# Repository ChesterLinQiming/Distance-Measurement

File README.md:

# Distance-Measurement

This project use GP2Y0A02YK0F which is Distance Measuring Sensor to measure the distance.

The range of it is 20-150cm.

The Circuit was designed by Qiming Lin.

This project also use AD7705, which is a two channel sigma delta converter, to convert the voltage from sensor

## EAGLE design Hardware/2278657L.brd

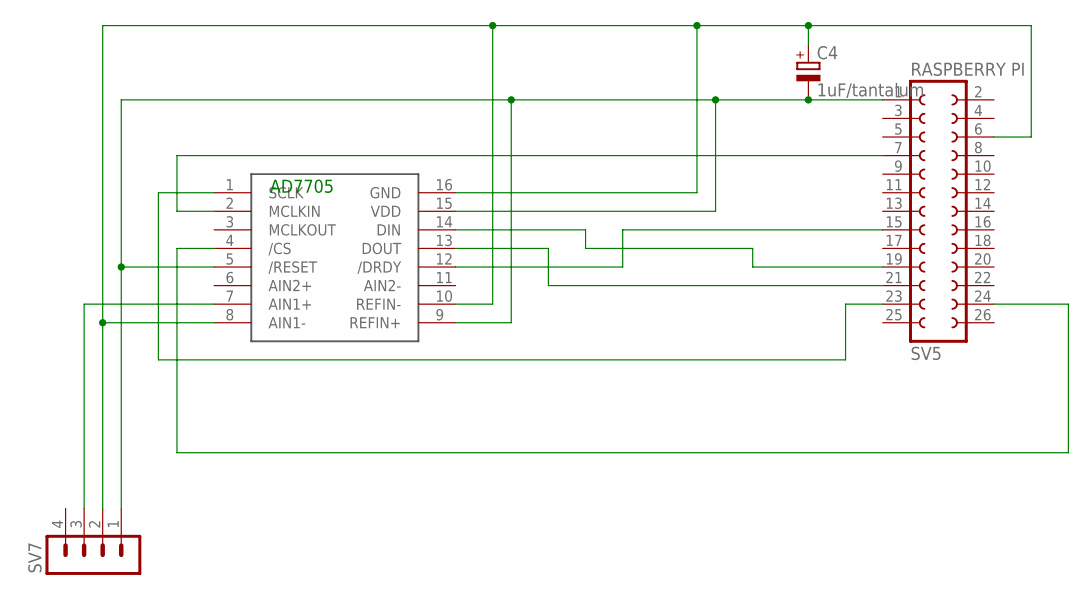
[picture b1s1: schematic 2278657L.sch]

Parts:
C4: 1uF/tantalum; TT2D7
SV5: RASPBERRY PI; FE13-2
SV7: MA04-1
U$3: AD7705; DIP16

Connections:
unnamed: SV5.7, U$3.2 (MCLKIN)
unnamed: SV7.3, U$3.7 (AIN1+)
unnamed: C4.+, SV5.6, SV7.2, U$3.8 (AIN1-), U$3.10 (REFIN-), U$3.16 (GND)
unnamed: SV5.23, U$3.1 (SCLK)
unnamed: C4.-, SV5.1, SV7.1, U$3.5 (/RESET), U$3.9 (REFIN+), U$3.15 (VDD)
unnamed: SV5.24, U$3.4 (/CS)
unnamed: SV5.15, U$3.12 (/DRDY)
unnamed: SV5.21, U$3.13 (DOUT)
unnamed: SV5.19, U$3.14 (DIN)

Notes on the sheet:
AD7705

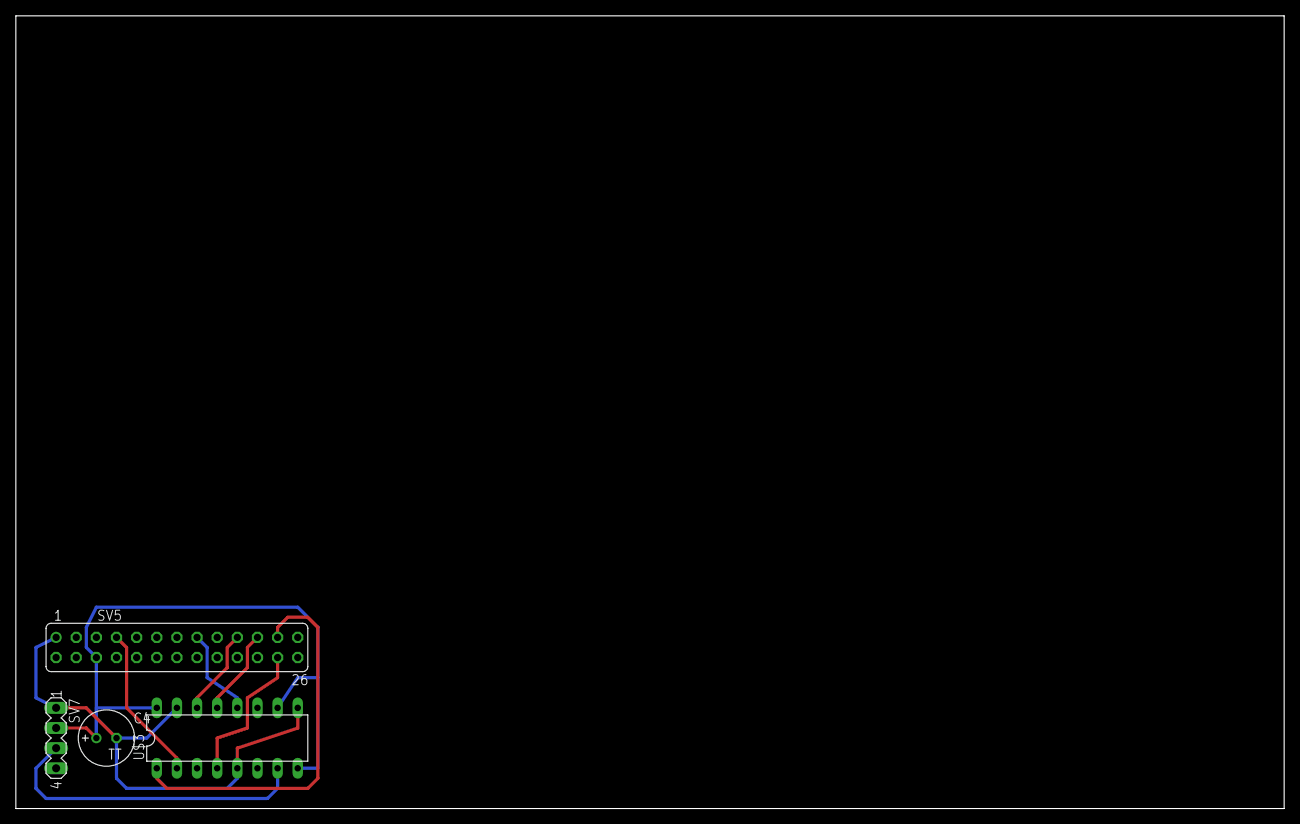
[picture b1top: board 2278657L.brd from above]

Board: 2 copper layers, 160.0 x 100.0 mm, 4 parts (0 on the bottom side), 9 nets.
